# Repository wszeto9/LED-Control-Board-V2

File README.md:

# LED-Control-Board-V2
Version 2 of a easy-to-deploy, low-cost PCBA to control LED lights over Wi-Fi. Designed for use at MIT's East Campus REX event to light up large forts and structures at distances of over 30 ft.

[Interactive BOM](https://htmlpreview.github.io/?https://raw.githubusercontent.com/wszeto9/LED-Control-Board-V2/main/breakout_boards/ibom.html)
<h2> Features:</h2>
<ul>

<li>Costs under $10 per Control board </li>
<li>USB-C PD/QC input (12V) for analog RGB strips</li>
<li>USB-C input (5V) for addressible RGB strips</li>
<li>Intended to be used with 12V/1.5A (18W) USB-C` power banks for portability</li>
<li>Panelized in a 4x2 panel of 100x100mm for minimal fabrication costs at JLCPCB</li>
<li>Individual PCBs are designed to be small and not noticible in deployment</li>
<li>Auto-reset circuit for ESP8266 reduces the equipment needed to program boards</li>
<li>Exposed breakout headers allows customization of voltages that are used</li>
<li>LEDs to debug circuits </li>
<li>Programming side (Right) can be cut off and seperated from controller side (Left) to reduce the chips needed to program boards to further reduce cost</li>
</ul>

Pinout

LED Indicators

Populated Board

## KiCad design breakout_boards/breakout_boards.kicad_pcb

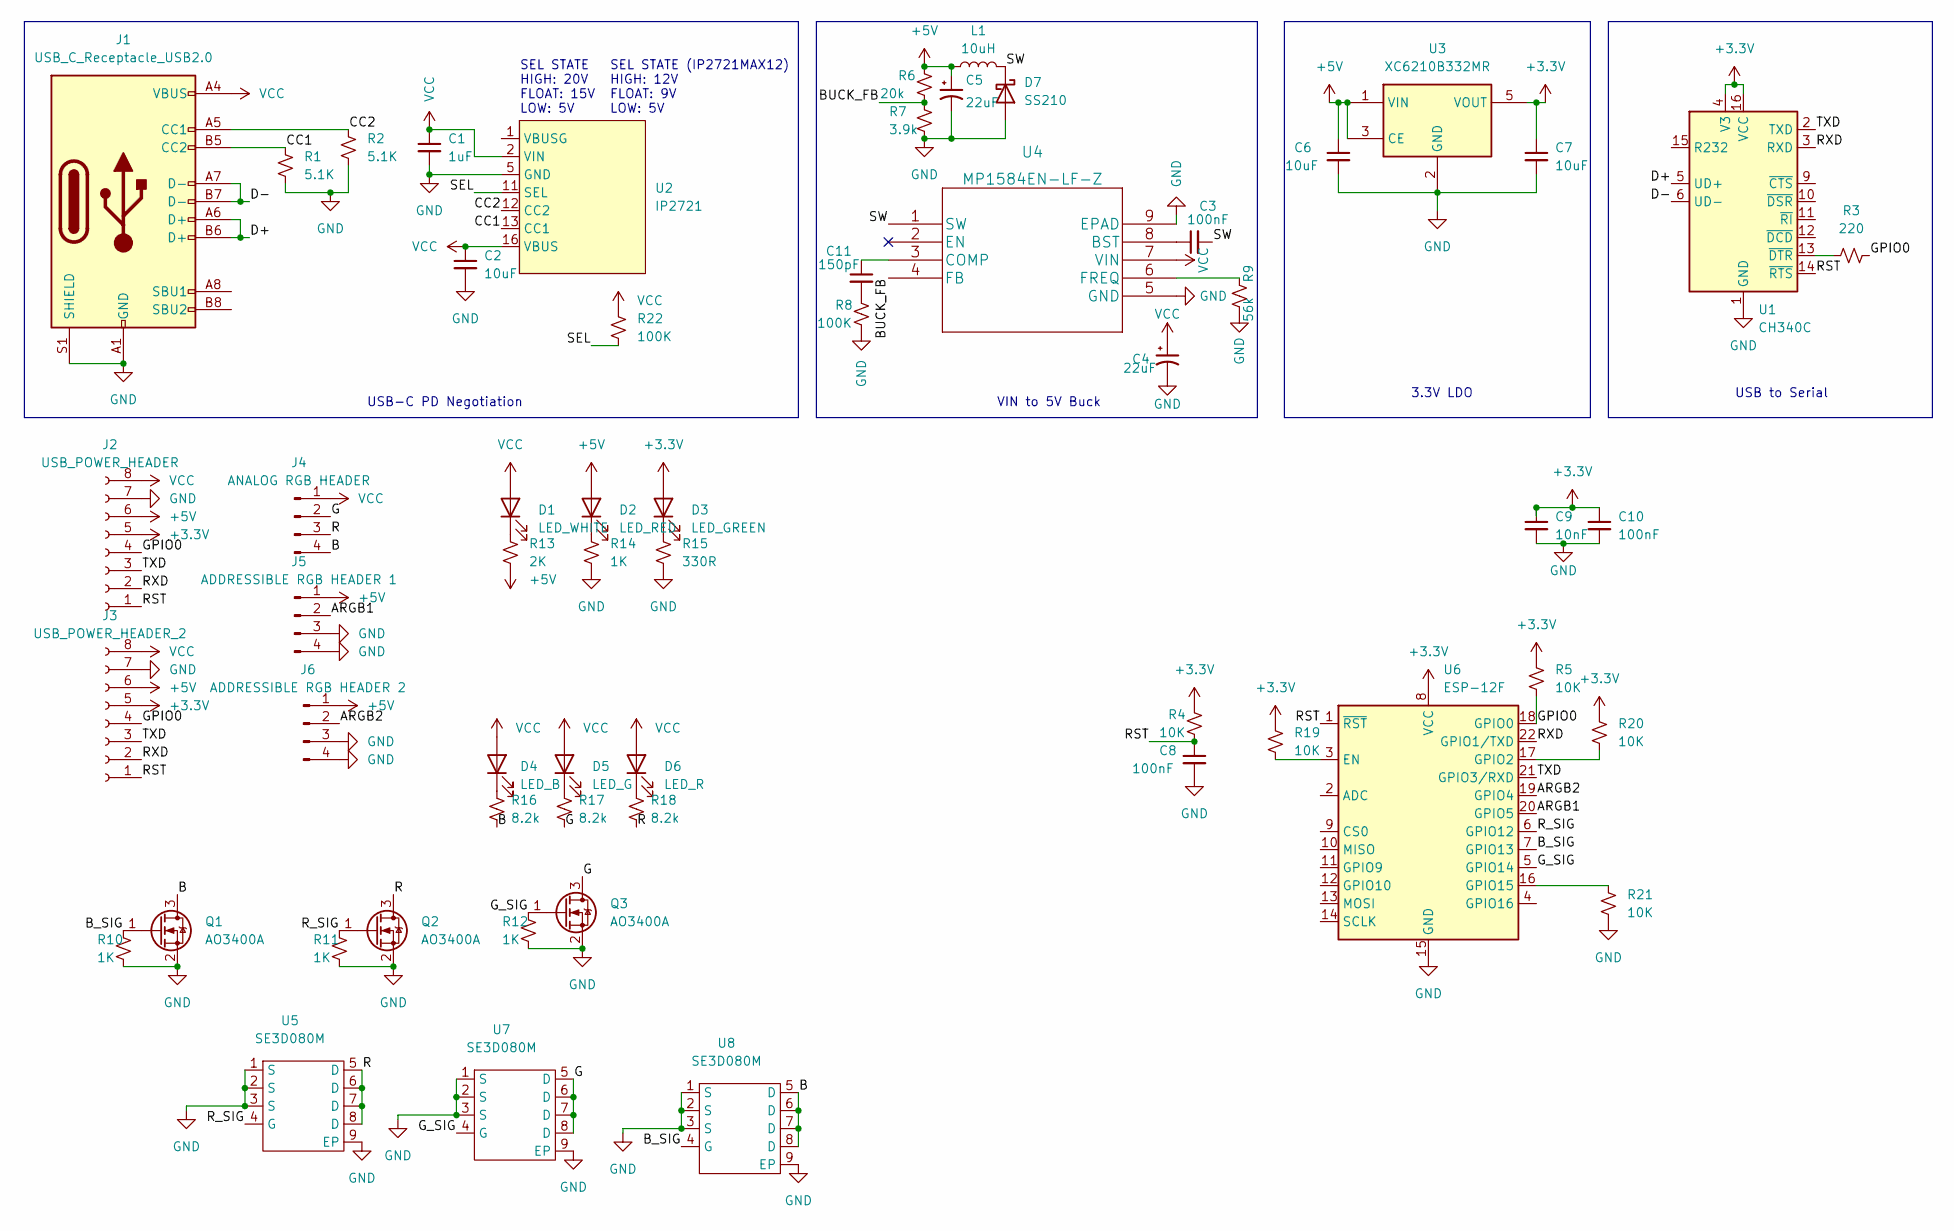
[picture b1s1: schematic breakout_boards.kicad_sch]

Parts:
C1: 1uF; C_0402_1005Metric; LCSC Part Number C52923
C2: 10uF; C_0603_1608Metric; LCSC Part Number C96446
C3: 100nF; C_0402_1005Metric; LCSC Part Number C52923
C4, C5: 22uF; C_0805_2012Metric; LCSC Part Number C45783
C6, C7: 10uF; C_0402_1005Metric; LCSC Part Number C15525
C8, C10: 100nF; C_0402_1005Metric; LCSC Part Number C1525
C9: 10nF; C_0402_1005Metric; LCSC Part Number C15195
C11: 150pF; C_0402_1005Metric; LCSC Part Number C52923
D1: LED_WHITE; LED_0603_1608Metric; LCSC Part Number C72038
D2: LED_RED; LED_0603_1608Metric; LCSC Part Number C2290
D3: LED_GREEN; LED_0603_1608Metric; LCSC Part Number C72043
D4: LED_B; LED_0603_1608Metric; LCSC Part Number C72043
D5: LED_G; LED_0603_1608Metric; LCSC Part Number C72043
D6: LED_R; LED_0603_1608Metric; LCSC Part Number C72043
D7: SS210; D_SMA
J1: USB_C_Receptacle_USB2.0; USB_C_Receptacle_Palconn_UTC16-G; LCSC Part Number C165948
J2: USB_POWER_HEADER; PinSocket_1x08_P2.54mm_Vertical
J3: USB_POWER_HEADER_2; PinSocket_1x08_P2.54mm_Vertical
J4: ANALOG RGB HEADER; PinHeader_1x04_P2.54mm_Vertical
J5: ADDRESSIBLE RGB HEADER 1; PinHeader_1x04_P2.54mm_Vertical
J6: ADDRESSIBLE RGB HEADER 2; PinHeader_1x04_P2.54mm_Vertical
L1: 10uH; L_Taiyo-Yuden_NR-40xx; LCSC Part Number C135263
Q1, Q2, Q3: AO3400A; SOT-23; LCSC Part Number C20917
R1, R2: 5.1K; R_0402_1005Metric; LCSC Part Number C25905
R3: 220; R_0603_1608Metric; LCSC Part Number C22962
R4, R5, R19, R20, R21: 10K; R_0402_1005Metric; LCSC Part Number C25744
R6: 20k; R_0402_1005Metric; LCSC Part Number C25741
R7: 3.9k; R_0402_1005Metric; LCSC Part Number C25762
R8, R22: 100K; R_0402_1005Metric; LCSC Part Number C25741
R9: 56k; R_0402_1005Metric; LCSC C25796
R10, R11, R12, R14: 1K; R_0402_1005Metric; LCSC Part Number C11702
R13: 2K; R_0402_1005Metric; LCSC Part Number C4109
R15: 330R; R_0402_1005Metric; LCSC Part Number C25104
R16, R17, R18: 8.2k; R_0402_1005Metric; LCSC Part Number C25104
U1: CH340C; SOIC-16_3.9x9.9mm_P1.27mm; LCSC Part Number C84681
U2: IP2721; TSSOP-16_4.4x5mm_P0.65mm; LCSC Part Number C603176
U3: XC6210B332MR; SOT-23-5; LCSC Part Number C424705
U4: MP1584EN-LF-Z; SOIC-8-1EP_3.9x4.9mm_P1.27mm_EP2.62x3.51mm
U5, U7, U8: SE3D080M; DFN-8-1EP_3x3mm_P0.65mm_EP1.55x2.4mm
U6: ESP-12F; ESP-12E

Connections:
+3V3: C7.1, C9.1, C10.1, D3.2 (A), J2.5, J3.5, R4.2, R5.1, R19.2, R20.1, U1.4 (V3), U1.16 (VCC), U3.5 (VOUT), U6.8 (VCC)
+5V: C5.1, C6.1, D2.2 (A), J2.6, J3.6, J5.1, J6.1, L1.1, R6.1, R13.2, U3.1 (VIN), U3.3 (CE)
/ARGB1: J5.2, U6.20 (GPIO5)
/ARGB2: J6.2, U6.19 (GPIO4)
/B: J4.4, Q1.3 (D), R16.2, U8.5 (D), U8.6 (D), U8.7 (D), U8.8 (D)
/BUCK_FB: R6.2, R7.1, U4.4 (FB)
/B_SIG: Q1.1 (G), R10.1, U6.7 (GPIO13), U8.4 (G)
/CC1: J1.B5 (CC2), R1.1, U2.13 (CC1)
/CC2: J1.A5 (CC1), R2.1, U2.12 (CC2)
/D+: J1.A6 (D+), J1.B6 (D+), U1.5 (UD+)
/D-: J1.A7 (D-), J1.B7 (D-), U1.6 (UD-)
/G: J4.2, Q3.3 (D), R17.2, U7.5 (D), U7.6 (D), U7.7 (D), U7.8 (D)
/GPIO0: J2.4, J3.4, R3.2, R5.2, U6.18 (GPIO0)
/G_SIG: Q3.1 (G), R12.1, U6.5 (GPIO14), U7.4 (G)
/R: J4.3, Q2.3 (D), R18.2, U5.5 (D), U5.6 (D), U5.7 (D), U5.8 (D)
/RST: C8.1, J2.1, J3.1, R4.1, U1.14 (~RTS), U6.1 (~RST)
/RXD: J2.2, J3.2, U1.3 (RXD), U6.22 (GPIO1/TXD)
/R_SIG: Q2.1 (G), R11.1, U5.4 (G), U6.6 (GPIO12)
/SEL: R22.2, U2.11 (SEL)
/SW: C3.2, D7.1 (K), L1.2, U4.1 (SW)
/TXD: J2.3, J3.3, U1.2 (TXD), U6.21 (GPIO3/RXD)
GND: C1.2, C2.2, C4.2, C5.2, C6.2, C7.2, C8.2, C9.2, C10.2, D7.2 (A), J1.A1 (GND), J1.A12 (GND), J1.B1 (GND), J1.B12 (GND), J1.S1 (SHIELD), J2.7, J3.7, J5.3, J5.4, J6.3, J6.4, Q1.2 (S), Q2.2 (S), Q3.2 (S), R1.2, R2.2, R7.2, R8.2, R9.2, R10.2, R11.2, R12.2, R14.2, R15.2, R21.2, U1.1 (GND), U2.5 (GND), U3.2 (GND), U4.5 (GND), U4.9 (EPAD), U5.1 (S), U5.2 (S), U5.3 (S), U5.9 (EP), U6.15 (GND), U7.1 (S), U7.2 (S), U7.3 (S), U7.9 (EP), U8.1 (S), U8.2 (S), U8.3 (S), U8.9 (EP)
unnamed: C3.1, U4.8 (BST)
unnamed: C11.1, U4.3 (COMP)
unnamed: C11.2, R8.1
unnamed: D1.1 (K), R13.1
unnamed: D2.1 (K), R14.1
unnamed: D3.1 (K), R15.1
unnamed: D4.1 (K), R16.1
unnamed: D5.1 (K), R17.1
unnamed: D6.1 (K), R18.1
unnamed: R3.1, U1.13 (~DTR)
unnamed: R9.1, U4.6 (FREQ)
unnamed: R19.1, U6.3 (EN)
unnamed: R20.2, U6.17 (GPIO2)
unnamed: R21.1, U6.16 (GPIO15)
VCC: C1.1, C2.1, C4.1, D1.2 (A), D4.2 (A), D5.2 (A), D6.2 (A), J1.A4 (VBUS), J1.A9 (VBUS), J1.B4 (VBUS), J1.B9 (VBUS), J2.8, J3.8, J4.1, R22.1, U2.2 (VIN), U2.16 (VBUS), U4.7 (VIN)

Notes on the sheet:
SEL STATE HIGH: 20V FLOAT: 15V LOW: 5V
VIN to 5V Buck
USB-C PD Negotiation
SEL STATE (IP2721MAX12) HIGH: 12V FLOAT: 9V LOW: 5V
USB to Serial
3.3V LDO

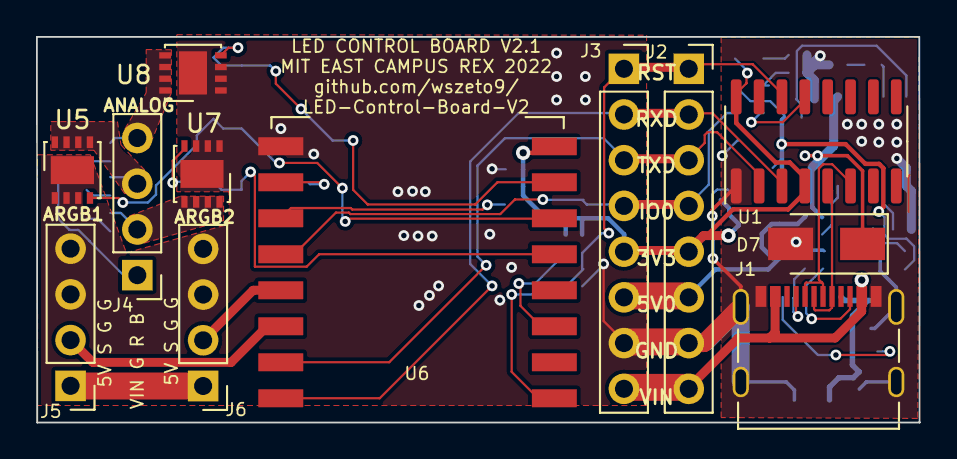
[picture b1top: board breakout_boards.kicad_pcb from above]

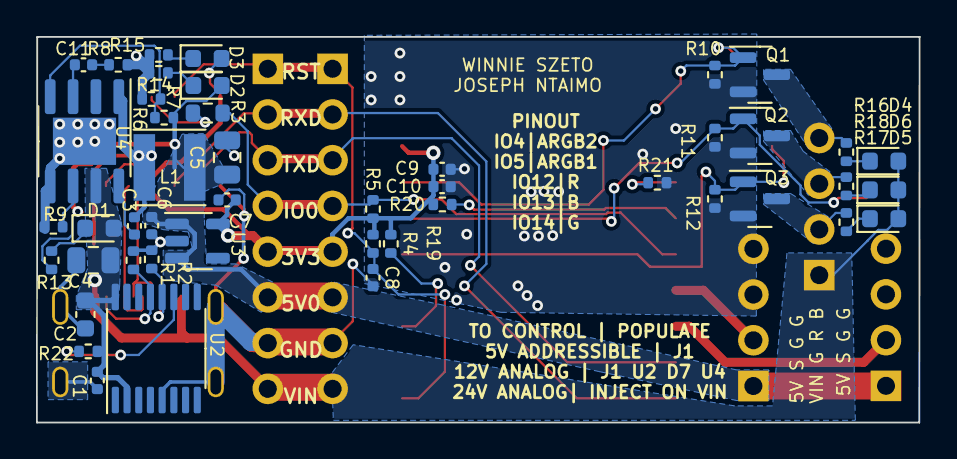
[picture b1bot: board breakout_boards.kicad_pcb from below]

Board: 2 copper layers, 49.0 x 21.4 mm, 58 parts (46 on the bottom side), 37 nets.

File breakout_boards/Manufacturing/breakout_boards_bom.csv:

Comment,Designator,Footprint,LCSC
"1uF","C1,C3","Capacitor_SMD:C_0402_1005Metric","C52923"
"10uF","C2","Capacitor_SMD:C_0603_1608Metric","C96446"
"22uF","C4,C5","Capacitor_SMD:C_0805_2012Metric","C45783"
"10uF","C6,C7","Capacitor_SMD:C_0402_1005Metric","C15525"
"100nF","C8,C10","Capacitor_SMD:C_0402_1005Metric","C1525"
"10nF","C9","Capacitor_SMD:C_0402_1005Metric","C15195"
"LED","D1,D2,D3,D4,D5,D6","LED_SMD:LED_0603_1608Metric","C72038"
"USB_C_Receptacle_USB2.0","J1","Connector_USB:USB_C_Receptacle_Palconn_UTC16-G","C165948"
"USB_POWER_HEADER","J2","Connector_PinSocket_2.54mm:PinSocket_1x08_P2.54mm_Vertical",""
"USB_POWER_HEADER_2","J3","Connector_PinSocket_2.54mm:PinSocket_1x08_P2.54mm_Vertical",""
"ANALOG RGB HEADER","J4","Connector_PinHeader_2.54mm:PinHeader_1x04_P2.54mm_Vertical",""
"ADDRESSIBLE RGB HEADER 1","J5","Connector_PinHeader_2.54mm:PinHeader_1x04_P2.54mm_Vertical",""
"ADDRESSIBLE RGB HEADER 2","J6","Connector_PinHeader_2.54mm:PinHeader_1x04_P2.54mm_Vertical",""
"10uH","L1","Inductor_SMD:L_Taiyo-Yuden_NR-40xx","C135263"
"AO3400A","Q1,Q2,Q3","Package_TO_SOT_SMD:SOT-23","C20917"
"5.1K","R1,R2","Resistor_SMD:R_0402_1005Metric","C25905"
"1K","R10,R11,R12,R14,R16,R17,R18","Resistor_SMD:R_0402_1005Metric","C11702"
"2K","R13","Resistor_SMD:R_0402_1005Metric","C4109"
"330R","R15","Resistor_SMD:R_0402_1005Metric","C25104"
"220","R3","Resistor_SMD:R_0603_1608Metric","C22962"
"10K","R4,R5,R9,R19,R20,R21","Resistor_SMD:R_0402_1005Metric","C25744"
"100K","R6,R22","Resistor_SMD:R_0402_1005Metric","C25741"
"18K","R7","Resistor_SMD:R_0402_1005Metric","C25762"
"12K","R8","Resistor_SMD:R_0402_1005Metric","C25752"
"CH340C","U1","Package_SO:SOIC-16_3.9x9.9mm_P1.27mm","C84681"
"IP2721","U2","Package_SO:TSSOP-16_4.4x5mm_P0.65mm","C603176"
"XC6210B332MR","U3","Package_TO_SOT_SMD:SOT-23-5","C424705"
"MT1470","U5","Package_TO_SOT_SMD:TSOT-23-6","C181781"
"ESP-12F","U6","RF_Module:ESP-12E",""

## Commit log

2022-03-28 added documentation
2022-06-18 V2.1
    Increased current capacity, changed modules to be 30V tolerant
2022-07-10 updated gitignore
2023-01-25 Created V3
2023-01-25 Revert "Created V3"
    This reverts commit 6f3930c4007686c3b7fe351275924e18ed986947.
